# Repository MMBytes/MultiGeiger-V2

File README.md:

# MultiGeiger V2 (ESP-IDF native)

A ground-up C rewrite of the [MultiGeiger](https://github.com/ecocurious2/MultiGeiger) radiation sensor firmware, ported from Arduino / PlatformIO to **native ESP-IDF 6.0**. Runs on **twelve** ESP32 / ESP32-S3 / ESP32-C5 board variants with a wide selection of optional environmental, particulate, noise, and ambient-light sensors. Uploads to **nine** public back-ends and publishes to MQTT (with Home Assistant Discovery) and remote syslog.

See the [releases page](https://github.com/MMBytes/MultiGeiger-V2/releases) for the latest build and per-release notes.

## What it does

- Counts Geiger pulses and computes CPM and µSv/h with a **runtime-selectable tube type** (Si22G / SBM-20 / SBM-19 / Unknown) configured on `/config` — no rebuild required.
- Drives the HV flyback boost converter from on-chip GPIO timing (no Arduino dependency).
- Optional **environmental sensing**: temperature, humidity, pressure, sea-level-adjusted pressure.
- Optional **PM (particulate matter)**: PM1 / PM2.5 / PM4 / PM10 plus number concentrations and typical particle size.
- Optional **noise**: LAeq / LAmin / LAmax dB(A).
- Optional **ambient light**: lux (two sensor families supported).
- Optional **air-quality index**: NOx index from a Sensirion SGP41 (log, `/status` and MQTT/Home Assistant only — no upload target carries it).
- Optional **standalone CSV logging** to a microSD card: one row of every attached sensor's readings per cycle, timestamped from the GNSS clock, for nodes deployed without a network.
- **Battery telemetry** (voltage, state of charge) on boards with an onboard MAX17048 fuel gauge.
- Optional **GNSS position display** — auto-detected PA1010D or MAX-M10S receiver shows fix, satellites, HDOP, lat/lon (OpenStreetMap link), and altitude on `/status`; display-only (NTP is the sole time source).
- Per-cycle upload (default 150 s, configurable 10 s – 1 h) to any subset of **nine** public back-ends.
- **MQTT publish** with 24 Home Assistant Discovery entities, three TLS modes including custom CA.
- **Remote syslog** (UDP 514, RFC 5424) for centralised log aggregation.
- **Hourly FTP/FTPS** upload of the on-device log ring buffer.
- **CPM history graph** on `/status` — 60-minute and 24-hour inline SVG with gridlines and a `HH:MM` time axis; rolling **cpm5 / cpm15** 5- and 15-minute averages fed to GMCMap and ThingSpeak.
- **Web UI** at `http://<device>/` — `/config` (settings), `/status` (live metrics + per-target TX stats + per-sensor presence + CPM graph), `/update` (OTA), `/log` (in-memory log ring). On PSRAM boards, ticking **Serve the web UI over HTTPS** on `/config` (off by default; applies after "Save and restart") moves the UI to `https://<device>/` with a per-device self-signed certificate (`/cert.pem` to import, SHA-256 fingerprint on `/`); port 80 then keeps `/log`, `/api/env` and `/cert.pem` plain and redirects everything else.
- **Crash recovery**: ESP-IDF panic handler writes a coredump to a dedicated flash partition; downloadable post-reboot via `GET /coredump.elf` (no USB required).
- **OLED status display** (SSD1306 128×64, also supports SparkFun SerLCD I²C and NeoPixel tick on supported boards).
- **NTP** with up to three configurable servers and POSIX TZ string.

## Supported hardware

### Boards (twelve build targets)

| Build target | MCU / module | Flash | Notes |
|---|---|---|---|
| `heltec_v2` | Heltec WiFi Kit 32 V2 (ESP32-D0WDQ6) | 8 MB | Onboard SSD1306 OLED. The original target — most production deployments. |
| `heltec_v2_4mb` | Heltec WiFi Kit 32 V2 clone | 4 MB | Same module silicon, smaller flash. Tight on heap during OTA — see V2.4.13 teardown logic in `main.c`. |
| `feathers3_d` | Unexpected Maker FeatherS3 with display (ESP32-S3) | 8 MB | Two STEMMA QT connectors (STEMMA1 on IO8/IO9, STEMMA2 LDO-gated on IO15/IO16). External I²C OLED via STEMMA. PSRAM — WiFi/lwIP/mbedTLS offloaded to PSRAM for sustained heap headroom. |
| `adafruit_qtpy_esp32_pico` | Adafruit QT Py ESP32-PICO | 8 MB | Compact form factor. Optional NeoPixel tick on pulse. PSRAM. |
| `seeed_xiao_esp32s3` | Seeed Studio XIAO ESP32-S3 | 8 MB | Tiny 21×17.5 mm — shares QT Py form factor + Geiger pin map (A0 / A1 / SCK), so one PCB design works for both. Onboard user LED blinks per pulse. PSRAM. |
| `seeed_xiao_esp32s3_wio` | Seeed Studio XIAO ESP32-S3 + Wio-SX1262 kit | 8 MB | The XIAO on Seeed's Wio-SX1262 LoRa board. **Rev C V3 carrier only** (Geiger pulse on the RX pad, since the LoRa SPI bus uses the SCK pad). **LoRaWAN uplink** (V2.8.11+), see below. The XIAO's user LED is not used (its pin is the Wio's button). PSRAM. |
| `heltec_wifi_lora32_v4_r2` | Heltec WiFi LoRa 32 V4 — base/R2 variant (ESP32-S3R2) | 16 MB | Third-party PCB: the standard Multigeiger V2 mainboard populated with this module instead of the Heltec V2. Onboard SSD1315 OLED on a dedicated, always-on I²C bus separate from the env-sensor bus. 2 MB in-package PSRAM. **LoRaWAN uplink** (V2.6.23+) via an onboard SX1262 (RadioLib 8.0, OTAA/Class A) — see the LoRaWAN section below. |
| `sparkfun_thing_plus_esp32s3` | SparkFun Thing Plus ESP32-S3, WRL-24408 (ESP32-S3-MINI-1) | 4 MB | Second-source MCU for the FeatherS3-D-format carrier PCB — same Feather footprint, drop-in alternative to `feathers3_d` on the same board. External I²C OLED via Qwiic, onboard MAX17048 fuel gauge, onboard WS2812 NeoPixel (always-on rail, no power-gate GPIO). 2 MB in-package PSRAM. |
| `sparkfun_thing_plus_esp32c5` | SparkFun Thing Plus ESP32-C5, WRL-30678 (ESP32-C5-WROOM-1) | 8 MB | First single-core/RISC-V target. Its own Thing Plus carrier (not a drop-in for the FeatherS3-D board). External I2C OLED via Qwiic, onboard MAX17048 fuel gauge, onboard WS2812 NeoPixel (always-on rail via pull-up, no power-gate GPIO). 8 MB in-package PSRAM. |
| `adafruit_esp32s3_tft_feather` | Adafruit ESP32-S3 TFT Feather, #5483 (ESP32-S3) | 4 MB | Shares the FeatherS3-D-format carrier PCB. Onboard 240×135 ST7789 color SPI TFT (esp_lcd, 5-page rotation only — no radiation single-page layout) instead of an external I²C OLED; shared TFT/STEMMA-QT power gate on GPIO21. Onboard WS2812 NeoPixel. 2 MB external QSPI PSRAM (feathers3_d-class, not in-package). |
| `adafruit_esp32_feather_v2` | Adafruit ESP32 Feather V2, #5400/#5900 (ESP32-PICO-MINI-02) | 8 MB | Second-source MCU (original ESP32 LX6, not S3) for the Feathers3d_new_pcb shared carrier. External I²C OLED wired to the header SDA/SCL pins, NOT the board's onboard STEMMA QT connector — NEOPIXEL_I2C_POWER only gates that connector's own regulator, and it isn't driven until neopixel_init() runs after sensor/display probing, so a display wired to the connector would never be found. Onboard WS2812 NeoPixel. No fuel gauge, so no battery telemetry (the board's GPIO35 battery divider is not read). 2 MB in-package PSRAM. |
| `adafruit_esp32s3_feather_4mb_2mbpsram` | Adafruit ESP32-S3 Feather, 4MB/2MB PSRAM, STEMMA QT, #5477 (ESP32-S3) | 4 MB | Shares the Feathers3d_new_pcb carrier PCB. No onboard display — external I²C OLED via STEMMA QT, probe-detected. Onboard MAX17048 fuel gauge, onboard WS2812 NeoPixel. Single STEMMA QT I²C bus power-gated on GPIO7 (no always-on bus) — same pattern as `adafruit_esp32s3_tft_feather`'s gate, different GPIO. Onboard red "#13" LED (not the NeoPixel) flashes on each Geiger pulse. 2 MB external QSPI PSRAM (feathers3_d-class, not in-package). |

Every build takes a `-DBOARD=<target>` argument — see [Build from source](#build-from-source). All boards share the same `main/` source tree; differences are isolated in per-board `sdkconfig.defaults.<board>` and HAL pin map. PSRAM boards additionally include `sdkconfig.defaults.psram` (WiFi roaming app + PSRAM offload knobs).

### LoRaWAN uplink (heltec_wifi_lora32_v4_r2 and seeed_xiao_esp32s3_wio)

OTAA/Class A uplink over an SX1262 (RadioLib 8.0; onboard on the Heltec V4, the Wio-SX1262 board on the XIAO ESP32-S3 kit), configured in a dedicated **`/config` LoRaWAN section** (all-region frequency-plan dropdown, DevEUI/JoinEUI/AppKey entry, join status; session keys persist in NVS across reboots). Ports 1 and 2 are byte-identical to the Multigeiger V1.9 Arduino firmware's TTN uplinks — paste `docs/ttn_payload_formatter.js` into TTN Console as a Custom Javascript payload formatter to decode them. While LoRaWAN runs, the upload interval follows the data rate instead of the configured interval (SF7 4 min, SF8 7, SF9 12, SF10 22, SF11 and SF12 30 min), which keeps the radiation frame at SF7–SF10 within TTN's Fair Use Policy of 30 s air time per day (the hourly environment frame and network-ordered repeats add to that); RadioLib's duty-cycle limiter is on as a backstop (EU868: the band's 1 %). The region defaults to AU915 — pick yours (e.g. EU868 in Europe) before enabling.

### Geiger tube

The tube type is a runtime **`/config` dropdown** — no rebuild required to switch tubes:

| Option | cps → µSv/h | Notes |
|---|---|---|
| **Unknown** | — (dose suppressed) | CPM reported; µSv/h field omitted from all uploads |
| **SBM-20** | 1 / 2.47 | Energy-compensated cylindrical tube |
| **SBM-19** | 1 / 9.81888 | Large pancake, lower background |
| **Si22G** | 1 / 12.2792 | **Default** — empirical vs. odlinfo.bfs.de reference |

Calibration factors from the upstream MultiGeiger (`ecocurious2 / t-pi tube.cpp`). The selected tube is shown on the `/status` Radiation card and in the boot config dump. Changing it in `/config` applies live (no reboot). CPM counting, HV timing, and dead-time gating are all tube-agnostic.

### Environmental sensors (auto-detected on I²C)

| Sensor | Address | Provides | Notes |
|---|---|---|---|
| **SHT45** | 0x44 | Temperature, humidity | Sensirion successor to SHT3x. PTFE filter variant supported. |
| **BME280** | 0x76 / 0x77 | Temperature, humidity, pressure | Bosch — original upstream sensor. |
| **BME688** | 0x76 / 0x77 | Temperature, humidity, pressure | Bosch — gas channel currently unused. |
| **BMP390** | 0x76 / 0x77 | Temperature, pressure | Bosch — high-accuracy barometric. |
| **BMP581** | 0x46 / 0x47 | Temperature, pressure | Bosch latest-gen — sub-Pa noise floor. |

The driver mix lets a node combine, e.g., SHT45 (best RH) + BMP581 (best pressure) on the same bus. The firmware picks the right reading per measurand from whichever sensors responded at boot.

### Specialty sensors (auto-detected on I²C)

| Sensor | Address | Provides | Notes |
|---|---|---|---|
| **Sensirion SPS30** | 0x69 | PM1 / PM2.5 / PM4 / PM10 mass, N05–N10 number concentrations, typical particle size | Adds the SPS30_* field group to all upload targets. |
| **hbitter DNMS** | 0x55 | LAeq / LAmin / LAmax dB(A) | Nettigo NAM-style Teensy-based noise module. Adds DNMS_noise_* fields. |
| **ALS-PT19** | (analog) | Ambient light (lux) | Onboard FeatherS3-D photodiode on ADC1_CH3. |
| **VEML7700** | 0x10 | Ambient light (lux) | Vishay I²C, alternative to ALS-PT19. |
| **PA1010D** | 0x10 | GNSS position + time (display-only) | Adafruit 4415 (MediaTek MT3333). Detected by live NMEA sniff — disambiguates from a VEML7700 at the same address. |
| **MAX-M10S** | 0x42 | GNSS position + time (display-only) | SparkFun Qwiic (u-blox DDC). Factory chip serial queried via UBX-SEC-UNIQID and shown on `/status`. |
| **Sensirion SGP41** | 0x59 | NOx index | VOC + NOx gas sensor; only the NOx index is surfaced (log / `/status` / MQTT). Runs its own sampling task — it needs a 1 Hz conditioning cadence. |
| **MAX17048** | 0x36 | Battery voltage, state of charge | Onboard fuel gauge on the FeatherS3-D, SparkFun Thing Plus and Adafruit Feather boards that carry one. |

A microSD socket (SDMMC 4-bit on ESP32-S3 boards, SPI where the chip has no SDMMC host) enables the standalone CSV logger when present; see `main/sd_logger.h` for the file layout.

### Displays

- **SSD1306 OLED** 128×64, I²C 0x3C or 0x3D — auto-probe both addresses (V2.4.19).
- **SparkFun SerLCD** (I²C variant) — alternative line-based display.
- **NeoPixel** tick-per-pulse on supported boards (configurable colour / brightness via `display_mode`).
- Built-in **speaker** click on pulse (configurable, off by default for sealed-tube installs).

## Upload targets

All **nine** targets are fully optional and independently configurable. Each has per-target circuit-breaker logic (V2.3.x) — 3 consecutive all-retry failures suspend that target for 20 cycles to prevent failed TLS handshakes from fragmenting heap.

| Target | Endpoint | Auth | Fields posted |
|---|---|---|---|
| **Madavi** | `api-rrd.madavi.de/data.php` (HTTP / HTTPS) | none | T/H/P; PM and noise are POSTed but the legacy server only graphs T/H/P |
| **sensor.community** | `api.sensor.community/v1/push-sensor-data/` (HTTP / HTTPS) | X-Sensor = chip ID | Radiation (X-PIN 19), T/H/P (11), PM (1), noise (15) — split bodies per pin |
| **Radmon** | `radmon.org/radmon.php?function=submit` (HTTP / HTTPS) | basic auth user/pw | Radiation CPM only |
| **openSenseMap** | `ingress.opensensemap.org/boxes/<BOX_ID>/data?luftdaten=1` (HTTPS) | Box ID in URL + optional raw access token (no `Bearer ` prefix) | Combined Luftdaten body |
| **aqi.eco** | `api.aqi.eco/update/<TOKEN>` (HTTPS) | token in URL | Combined Luftdaten body with `esp8266id` field |
| **GMCMap** | `gmcmap.com/log2.asp` (HTTP only) | Account ID + Geiger counter ID in URL | Radiation CPM + ACPM (5-min rolling average). Skipped when tube disabled. |
| **ThingSpeak** | `api.thingspeak.com/update` (HTTP / HTTPS) | Write API key | field1=CPM, field2=µSv/h, field3=cpm5, field4=cpm15, field5–7=T/H/P. Skipped when tube disabled. |
| **ThingSpeak PM** | `api.thingspeak.com/update` (HTTP / HTTPS) | Separate write API key | field1–4=PM1/PM2.5/PM4/PM10, field5–7=T/H/P, field8=typical particle size. Skipped when no PM sensor. |
| **openSenseMap STAGING** | `upload.staging.opensensemap.org/boxes/<BOX_ID>/data?luftdaten=1` (HTTPS only) | Independent Box ID + access token | Same Luftdaten body as production OSM — lets a node mirror to prod + staging simultaneously. |

Each target shows live per-target stats on `/status` — attempted / succeeded counters, last HTTP status, last attempt time, current breaker state.

Cert verification uses the Mozilla CA bundle baked into flash. Per-target "insecure mode" available for self-hosted instances. TLS 1.2 and TLS 1.3 both supported.

## Observability

### MQTT (V2.4.2–V2.4.6)

Publish-only MQTT 3.1.1 client with three TLS modes:

- **Mode 0** — plain TCP (broker on LAN)
- **Mode 1** — TLS via Mozilla CA bundle (public broker)
- **Mode 2** — TLS via user-supplied custom CA PEM (self-signed broker, e.g. a Pi running Mosquitto on the LAN)

When `mqtt_ha_discovery` is enabled (default), the firmware publishes 24 Home Assistant Discovery entities at boot — radiation, all detected sensors, WiFi RSSI, per-target TX stats, etc. — auto-gated on driver presence. HA picks them up without manual configuration.

Topic layout: `<prefix>/<chip-id>/state` (full state JSON every cycle) plus `<prefix>/<chip-id>/availability` for the LWT.

### Syslog (V2.4.15)

UDP syslog client (port 514, configurable). **RFC 5424** framing with `local0` facility. Every applog line mirrors to syslog when enabled. Before the wall clock is valid (pre-NTP sync), the timestamp is the NILVALUE `-` — a stock rsyslog collector falls back to its own receive time, correctly dating boot-banner and config-dump lines. Once NTP has synced, the timestamp is local RFC 3339 with a numeric UTC offset (e.g. `2026-06-13T20:45:50+10:00`), matching the in-message device time shown on `/status`. The per-cycle log line reports `syslog udp: tx=N drops=M` so device-side UDP packet loss is visible (V2.5.29).

### FTP / FTPS log upload (V2.0.x +)

Configurable interval (1 min – 10 090 min, ~7 days; default hourly) upload of the on-device log ring buffer to an FTP server. TLS supported (FTPS explicit-mode, AUTH TLS, TLS 1.2 and 1.3 both work). Cleared after successful upload; carried over across reboot via NVS.

### CPM history graph (V2.5.6)

Two-tier in-RAM ring: 60 one-minute samples + 24 one-hour samples (~250 bytes, all boards). Sampled from a monotonic pulse counter independent of the destructive per-cycle `tube_read()`, so the TX interval has no effect on graph resolution. Displayed as an **inline SVG** on `/status` with horizontal CPM gridlines and a `HH:MM` time axis. Also drives the **cpm5 / cpm15** rolling averages (means of the last 5 / 15 minute samples), fed to GMCMap as ACPM and to ThingSpeak as field3 / field4.

### Coredump on panic (V2.4.18)

64 KB dedicated coredump partition. The ESP-IDF panic handler writes the panicking task's register state + stack snapshot before reset. Recoverable post-reboot via `GET /coredump.elf` (basic auth gated) — no USB needed once flashed. Decode with `espcoredump.py`.

## Security

V2.3.33 web security audit + V2.4.x follow-ups (see CHANGELOG):

- **Basic auth** on `/config`, `/update`, `/reboot`, `/coredump.elf` (user `admin`, password = configured AP password).
- **Constant-time password comparison** to defeat timing oracles.
- **CSRF protection**: POSTs to `/config` / `/update` / `/reboot` require an `Origin` header matching the device's URL — protects against drive-by browser POSTs. **Note for curl users**: add `-H "Origin: http://device:port"` or you'll get a 403.
- **OTA size clamp**: rejects an image larger than the target OTA slot before writing (2 MB on 8 MB-flash boards, 1.875 MB on 4 MB-flash boards).
- **X-Frame-Options: DENY** on all responses.
- **TX is paused during OTA** (V2.4.24): scheduled cycles skip while an OTA upload is in progress, giving the OTA the full WiFi airtime.

- **HTTPS for the device UI** (V2.8.0, PSRAM boards): optional, per-device self-signed certificate, see "What it does" above.

Deferred for future work: signed OTA images, NVS encryption, rate limiting. The device is designed for a trusted LAN; do not expose it to the internet.

## Installation

### Flashing a prebuilt release (no build environment needed)

Every [release](https://github.com/MMBytes/MultiGeiger-V2/releases) attaches per-board artefacts. Pick the bundle that matches your board — see the release notes for the file naming.

**Browser-based first flash (no tools needed):** The [MultiGeiger-V2 web flasher](https://mmbytes.github.io/MultiGeiger-V2/) supports Chrome / Edge via the WebSerial API — connect the board over USB, select your board, and flash the latest release directly from the browser.

**`esptool` first flash:** Install [`esptool`](https://github.com/espressif/esptool) (`pip install esptool`); replace `COM3` with your actual serial port.

**First flash of a blank / fresh / bricked device — use `geiger_v2_merged_<board>.bin`:**

```
esptool --chip esp32 --port COM3 write-flash 0x0 geiger_v2_merged_heltec_v2.bin
```

Use `--chip esp32s3` for the ESP32-S3 boards and `--chip esp32c5` for the SparkFun Thing Plus ESP32-C5. FeatherS3-D additionally needs `--before no-reset --after no-reset` and the BOOT+RST button dance.

The merged image bundles the bootloader, partition table, OTA slot pointer, and the app at their correct flash offsets — a single-file factory flash. Each release also attaches the separate parts (`bootloader_<board>.bin`, `partition-table_<board>.bin`, `ota_data_initial_<board>.bin`), the matching debug symbols (`elf_<board>.zip`, for decoding a coredump) and a `SHA256SUMS` file.

**Upgrading a device already running this firmware:**

- **OTA (recommended)** — browse to `http://<device-ip>/update`, log in (`admin` / your configured AP password), pick the `geiger_v2_<board>.bin` artefact for your board. No cable, keeps your NVS (WiFi credentials, MQTT broker, etc.) intact.
- **Board revision matters**: the firmware has no runtime board-revision detection. Before flashing an older carrier or mainboard, read the compatibility table in [`Hardware/README.md`](Hardware/README.md).

### First boot

The device comes up as a WPA2-protected WiFi access point named after its chip ID (`esp32-<number>`, e.g. `esp32-1234567`). The AP password is the configured AP password — `ESP32Geiger` on a fresh device. Join it, browse to `http://192.168.4.1/config`, and set WiFi credentials, the AP/admin password and your back-end choices. The AP stays up for about two minutes after boot; after that window, or a manual reboot, the device joins your network in STA mode.

Default credentials (change these on first login — the same password protects the web UI and the setup AP):

| Field | Default |
|---|---|
| Username | `admin` |
| Password | `ESP32Geiger` |

**Locked out of the web page?** After 5 wrong passwords in a row the node refuses every login for a while, the correct password too (1 minute at first, doubling with each further lock up to 8 h 32 min). Wait until the time shown has passed, or press the reset button or unplug the node for about 10 seconds; that clears the lock.

**Stored passwords on `/config`:** the page never shows them. A field shows `******** SECRET SET ********` when a value is stored; leave it empty to keep it, enter `-` to clear it, or type a new value.

## Build from source

Needed only if you want to modify the firmware.

### Requirements

- [ESP-IDF v6.0.3](https://docs.espressif.com/projects/esp-idf/en/stable/esp32/get-started/index.html) — pure IDF, not arduino-esp32, not PlatformIO. Releases are built with exactly v6.0.3; CMake warns if a different IDF is in use.
- A Windows / Linux / macOS host with the IDF tools installed
- USB cable with data lines

### Commands

With the IDF environment sourced (`export.ps1` on Windows, `export.sh` on Linux/macOS):

```
idf.py -B build_heltec_v2 -DBOARD=heltec_v2 build
idf.py -B build_heltec_v2 -DBOARD=heltec_v2 -p <PORT> flash monitor
idf.py -B build_heltec_v2 -DBOARD=heltec_v2 merge-bin -o geiger_v2_merged_heltec_v2.bin   # single-file factory image
```

`-DBOARD=` selects the chip target, the board macros and the per-board `sdkconfig.defaults.<board>` overlay in one go — do not pass `SDKCONFIG_DEFAULTS` yourself. Substitute `heltec_v2_4mb`, `feathers3_d`, `adafruit_qtpy_esp32_pico`, `seeed_xiao_esp32s3`, `seeed_xiao_esp32s3_wio`, `heltec_wifi_lora32_v4_r2`, `sparkfun_thing_plus_esp32s3`, `sparkfun_thing_plus_esp32c5`, `adafruit_esp32s3_tft_feather`, `adafruit_esp32_feather_v2`, or `adafruit_esp32s3_feather_4mb_2mbpsram` for other boards, and use a matching `-B build_<board>` directory: the generated `sdkconfig.<board>` cache is per board, so boards never pollute each other.

Host-side unit tests for the pure helpers need only a C compiler:

```
gcc -I main -Wall -Wextra -Werror -std=c11 -o test/run test/test_main.c && ./test/run
```

(`_test.cmd` wraps the same on Windows.) Static analysis runs in CI with cppcheck 2.22.0, one leg per board.

Optional: `git config core.hooksPath .githooks` enables a pre-commit scan that refuses to commit private-network data (LAN/MAC/hostname shapes) — the same check CI runs on every push.

### Release workflow

`git tag -a V2.X.Y && git push --tags` is the release ceremony. GitHub Actions `release.yml` first runs the cheap gates (host tests, cppcheck on every board, a `## V2.X.Y` section present in `CHANGELOG.md`), then builds all twelve boards (each build also verifies that `VERSION_STR` equals the tag and that the image fits its OTA slot), creates the GitHub Release with the artefacts, `SHA256SUMS` and the CHANGELOG section as body, and finally publishes the web flasher — only if the tag is the newest release, so re-running an old tag never rolls the flasher back.

## Repository layout

```
main/                       firmware C sources
  main.c                    entry point, WiFi state machine, cycle loop
  tube.c                    pulse ISR + HV driver timing
  tube_types.c / .h         tube characteristics table (cps→µSv/h factors per tube type)
  tube_pcnt.c / .h          optional PCNT width-filter for narrow-pulse characterisation
  tube_logic.h              pure inline helpers: clamp_u32, gmc_classify, guard policy
  config.c / config_fields.def
                            NVS-backed config, X-macro schema
  http_server.c             web UI (/, /config, /status, /update, /log, /coredump.elf)
  transmission.c            upload pipeline: Madavi / SC / Radmon / OSM / aqi / GMC / ThingSpeak
  mqtt.c / mqtt_discovery.c MQTT 3.1.1 publish + HA Discovery
  syslog.c                  RFC 5424 UDP syslog client
  log_ftp.c                 FTP/FTPS log upload
  net_arp.c                 gratuitous ARP (mesh-AP blackhole prevention)
  periodic.c                housekeeping (PSA refresh + ARP safety-net)
  coredump.c                /coredump.elf streaming from partition
  ntp.c                     SNTP with configurable POSIX TZ string
  history.c / .h            in-RAM CPM history ring + cpm5/cpm15 rolling averages
  gnss.c / .h               GNSS driver: PA1010D + MAX-M10S auto-detected, display-only
  env_sensor.c              umbrella for T/H/P drivers
  sht45.c bmp581.c bmp390.c bme688.c bme280.c
                            individual T/H/P drivers
  pm_sensor.c sps30.c       particulate matter
  noise_sensor.c dnms.c     noise (DNMS / NAM)
  als.c veml7700.c          ambient light
  sgp41.c                   SGP41 NOx index (+ sensirion_crc.h, sensirion_gas_index_algorithm.c)
  fuel_gauge.c              MAX17048 battery fuel gauge
  sd_card.c sd_logger.c     microSD mount + standalone CSV logger
  lorawan.cpp lorawan_codec.h
                            LoRaWAN uplink (heltec_wifi_lora32_v4_r2, seeed_xiao_esp32s3_wio)
  telemetry.c / .h          sensor-reading registry shared by SD logger and status
  env_api.h                 /api/env JSON contract (served by http_server.c)
  tls_cert.c / tls_logic.h  per-device HTTPS certificate (generation, NVS storage)
  display.c display_tft.c display_serlcd.c neopixel.c led.c
                            display drivers (OLED / ST7789 TFT / SerLCD) + LED pulse-tick
  speaker.c / speaker_logic.h
                            pulse tick (boards with speaker)
  i2c_bus.c                 shared I²C bus handle + mutex
  applog.c                  in-memory log ring buffer
  diag.c / .h               I²C error counter + per-cycle heap split logging
  util.h                    clamped string helpers, URL encoding
  hal.h                     per-board pin map + capability flags
  sysinfo.h                 chip model string, reset-reason string
  main_status.h             request-restart IPC (main loop ← HTTP/TX workers)
partitions.csv              factory + dual-OTA (2 MB each) + coredump (64 KB) on 8 MB flash
partitions_4mb.csv          dual-OTA (1.875 MB each) + coredump for the four 4 MB-flash boards
                            (heltec_v2_4mb, sparkfun_thing_plus_esp32s3,
                            adafruit_esp32s3_tft_feather, adafruit_esp32s3_feather_4mb_2mbpsram)
sdkconfig.defaults.<board>  per-board IDF configuration
sdkconfig.defaults.psram    shared WiFi-roaming app + PSRAM-offload knobs (PSRAM boards)
CHANGELOG.md                per-release WHAT/WHY notes
docs/                       web flasher (index.html + manifests/ + vendored esp-web-tools),
                            TTN payload formatter
.github/workflows/          build.yml, release.yml, repo-checks.yml + the reusable
                            _host-test / _cppcheck / _build-boards gates
.github/scripts/            board-list consistency check, private-data scan,
                            CHANGELOG section extractor

Hardware/                   PCB design files — see Hardware/README.md for the
                            revision → board → minimum-firmware map
  Revision_A/               MultiGeiger V1.10 mainboard for the Heltec WiFi LoRa 32 V4 (Eagle)
  Revision_B/               FeatherS3-D-format carrier PCB (KiCad 8)
    geiger.kicad_pro / .kicad_pcb / .kicad_sch
                            KiCad 8 project sources
    0_Custom_Library.pretty / geiger.pretty
                            custom symbol + footprint libraries
    3d-Files/               3D STEP models for non-trivial parts
    Deliverables/
      Gerber Files/         fab-ready Gerbers
      Pick And Place Files/ assembly CSVs
      BOM/                  bill of materials
      Schematic/            schematic PDF
      Renderings/           3D rendered previews
      Supporting Files/     STEP export
  Revision_C/               shared-footprint PCB: QT Py ESP32-PICO or XIAO ESP32-S3
    (same sub-structure as Revision_B)
```

## PCB design files

Three PCB revisions are included in the `Hardware/` directory. [`Hardware/README.md`](Hardware/README.md) maps each revision to the modules it carries and the **minimum firmware** it needs — read it before flashing an older board.

### Revision A — MultiGeiger V1.10 mainboard

[`Hardware/Revision_A/`](Hardware/Revision_A/) is the Eagle project for the V1.10 iteration of the upstream MultiGeiger mainboard, re-laid for the Heltec WiFi LoRa 32 V4 (R2) module (`heltec_wifi_lora32_v4_r2` firmware, V2.7.1 or later), with Gerbers, pick-and-place CSV, BOM, schematic PDF and renderings.

- **Browse the schematic**: [`Hardware/Revision_A/Deliverables/Schematic/geiger-v2.pdf`](Hardware/Revision_A/Deliverables/Schematic/geiger-v2.pdf)

### Revision B — FeatherS3-D-format carrier

[`Hardware/Revision_B/`](Hardware/Revision_B/) is the full KiCad 8 project for the Feather-format carrier PCB (FeatherS3-D, SparkFun Thing Plus ESP32-S3 and the three Adafruit Feather targets share it), plus fabrication-ready Gerbers, pick-and-place CSVs, schematic PDF, BOM, and 3D STEP exports. Si22G tube; full BOM uses metal-film resistors and polypropylene HV capacitors throughout.

- **Browse the schematic**: [`Hardware/Revision_B/Deliverables/Schematic/geiger.pdf`](Hardware/Revision_B/Deliverables/Schematic/geiger.pdf)
- **3D renderings**: [`Hardware/Revision_B/Deliverables/Renderings/`](Hardware/Revision_B/Deliverables/Renderings/)
- **Re-fabricate at JLCPCB or similar**: upload the Gerbers + PnP CSV from `Deliverables/` directly, or open the `.kicad_pro` to regenerate

### Revision C — shared QT Py / XIAO footprint

[`Hardware/Revision_C/`](Hardware/Revision_C/) is a shared-footprint PCB that accepts either the Adafruit QT Py ESP32-PICO or the Seeed XIAO ESP32-S3 in the same U1 socket — both use the same Geiger pin map (HV_FET / GMC / interrupt on A0 / A1 / SCK), so one board runs both `adafruit_qtpy_esp32_pico` and `seeed_xiao_esp32s3` firmware builds. Same HV circuit as Revision B; no piezo (sealed-tube form factor). On-board Qwiic / STEMMA QT connector with on-board pull-ups.

- **Browse the schematic**: [`Hardware/Revision_C/Deliverables/Schematic/geiger.pdf`](Hardware/Revision_C/Deliverables/Schematic/geiger.pdf)
- **3D renderings**: [`Hardware/Revision_C/Deliverables/Renderings/`](Hardware/Revision_C/Deliverables/Renderings/)
- **Re-fabricate**: upload Gerbers + PnP CSV from `Revision_C/Deliverables/`

**License** for all three revisions: same GPL-3.0-or-later as the firmware.

## Documentation

- **Per-release notes**: [`CHANGELOG.md`](CHANGELOG.md) — full WHAT/WHY for every release since V2.3.23, headlines for older. GitHub release pages have the rest.
- **In-firmware**: `/status` shows live state including which drivers responded at boot, per-target TX stats, FTP / MQTT / syslog status, CPM history graph, and GNSS position if a receiver is detected.

## Attribution

This firmware is an **independent rewrite** of [MultiGeiger](https://github.com/ecocurious2/MultiGeiger) by the ecocurious2 project. Hardware design, sensor-community protocol compatibility, the Si22G calibration constant, and the upload-target conventions come from upstream; the C source in this repository shares no commits with it.

The MQTT / HA Discovery, MQTT TLS modes, openSenseMap support, aqi.eco support, GMCMap support, ThingSpeak support, syslog (RFC 5424), coredump-to-flash, multi-board build (FeatherS3 / QT Py / XIAO), runtime-selectable tube type, PCNT width filter, dead-time guard, CPM history graph and rolling averages, GNSS display, and most of the additional sensor drivers (SHT45, BMP581, BMP390, BME688, SPS30, DNMS, ALS-PT19, VEML7700, PA1010D, MAX-M10S) are net-new in V2.

## License

**GPL-3.0-or-later** — same as upstream MultiGeiger. See [LICENSE](LICENSE).

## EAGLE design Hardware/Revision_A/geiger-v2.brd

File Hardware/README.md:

# Hardware

PCB designs that the MultiGeiger V2 firmware runs on. Three revisions are
tracked. Each is a complete design with fabrication outputs under its
`Deliverables/` folder: Gerbers (plus an order-ready zip), pick-and-place
CSV, BOM, schematic PDF and 3D renderings.

## Revision → board → firmware

| Directory | Board | Module it carries | Firmware target(s) | Minimum firmware | Tool |
|---|---|---|---|---|---|
| `Revision_A/` | MultiGeiger mainboard **V1.10** | Heltec WiFi LoRa 32 V4, base/R2 variant | `heltec_wifi_lora32_v4_r2` | **V2.7.1** | Eagle (`geiger-v2.sch` / `.brd`) |
| `Revision_B/` | FeatherS3-D-format carrier, **V2 layout** | Unexpected Maker FeatherS3-D, SparkFun Thing Plus ESP32-S3, Adafruit ESP32-S3 TFT Feather, Adafruit ESP32 Feather V2, Adafruit ESP32-S3 Feather #5477 | `feathers3_d`, `sparkfun_thing_plus_esp32s3`, `adafruit_esp32s3_tft_feather`, `adafruit_esp32_feather_v2`, `adafruit_esp32s3_feather_4mb_2mbpsram` | **V2.6.34** | KiCad 8 |
| `Revision_C/` | Shared-footprint carrier, **V2 layout** | Adafruit QT Py ESP32-PICO **or** Seeed XIAO ESP32-S3 in the same U1 socket (the XIAO ESP32-S3 + Wio-SX1262 kit needs the V3 layout, see below) | `adafruit_qtpy_esp32_pico`, `seeed_xiao_esp32s3` (V3 layout: also `seeed_xiao_esp32s3_wio`) | **V2.6.34** | KiCad 8 |

Not in this directory:

- The Heltec WiFi Kit 32 V2 targets (`heltec_v2`, `heltec_v2_4mb`) run on the
  upstream [ecocurious2 MultiGeiger](https://github.com/ecocurious2/MultiGeiger)
  mainboard (V1.4, Eagle files in that repository's `docs/hardware/`).
- The SparkFun Thing Plus ESP32-C5 target has its own carrier; that design is
  not published here.

## Firmware compatibility — read before flashing

There is no runtime board-revision detection: **the firmware version is the
cutover line.** The pin maps live in `main/hal.h`, whose header comment is
the authoritative statement of this rule.

- **Rev B V2 and Rev C V2 layouts (the files tracked here)** need firmware
  **≥ V2.6.34**. That release moved the Geiger count and HV-FET signals to
  different socket pads to remove HV-to-counter crosstalk.
- **The original (pre-V2) Rev B / Rev C layouts** must stay on firmware
  **≤ V2.6.33**. Flashing a newer build onto an original carrier drives the
  HV FET PWM into the tube pickup and reads "counts" off the FET gate trace.
  Those layouts are superseded and not tracked.
- **Rev C V3 layout** (not yet published here) moves the Geiger count signal
  from socket pad 9 (SCK) to pad 8 (RX), so that pads 9 to 11 are free for an
  SPI add-on such as the Wio-SX1262 LoRa board on the XIAO ESP32-S3. It needs
  firmware **≥ V2.8.10** with `/config` → **Rev C carrier = V3**. The setting
  defaults to V2, so a Rev C V2 carrier needs no change. It must match the
  carrier. The XIAO ESP32-S3 + Wio-SX1262 kit has its own firmware target,
  `seeed_xiao_esp32s3_wio` (≥ **V2.8.11**), which is built for the V3 layout
  only and has no carrier setting.
- **V1.10 mainboard (Revision A)** needs firmware **≥ V2.7.1**. V2.6.34 was
  written against a pre-fabrication pad assignment that was never
  manufactured, so for this target V2.6.34 matches no physical board.
- **V1.9 mainboard** (an earlier third-party respin for the same module, not
  tracked) stays on **≤ V2.6.33**.

The browser flasher always installs the latest release, so it is only
suitable for the Rev B V2 / Rev C V2 layouts, the Rev C V3 layout and the
V1.10 mainboard.

## Provenance

- **Revision A** is the V1.10 iteration of the upstream MultiGeiger mainboard
  lineage (ecocurious2 V1.4 → a third-party V1.9 respin for the Heltec WiFi
  LoRa 32 V4 module → this V1.10 rework: HV_CAP_FULL moved from GPIO2 to
  GPIO3 and GMC_COUNT to GPIO6 — the V2.6.34 design had those two the other
  way round and was never built — piezo on GPIO4/5). Kept in Eagle like its
  ancestors.
- **Revision B** and **Revision C** are this project's own KiCad 8 designs.
  They keep the upstream HV topology (flyback boost, zener-regulated rail,
  Si22G tube) and add module sockets, a Qwiic / STEMMA QT connector and
  (Rev C) a sealed, speaker-less form factor. The "V2 layout" of each is the
  current file; the first layout was replaced after the crosstalk
  investigation described in `main/hal.h`.

BOM part numbers are maintained at the source — the Revision A BOM is
generated, the Revision B / C part numbers live in a schematic field pushed
to the footprints — so edit there, not in the exported CSVs.

## Licence

All three designs: **GPL-3.0-or-later**, the same licence as the firmware
and as the upstream MultiGeiger project they descend from. See the
repository [LICENSE](../LICENSE). Upstream attribution: ecocurious2 /
MultiGeiger.

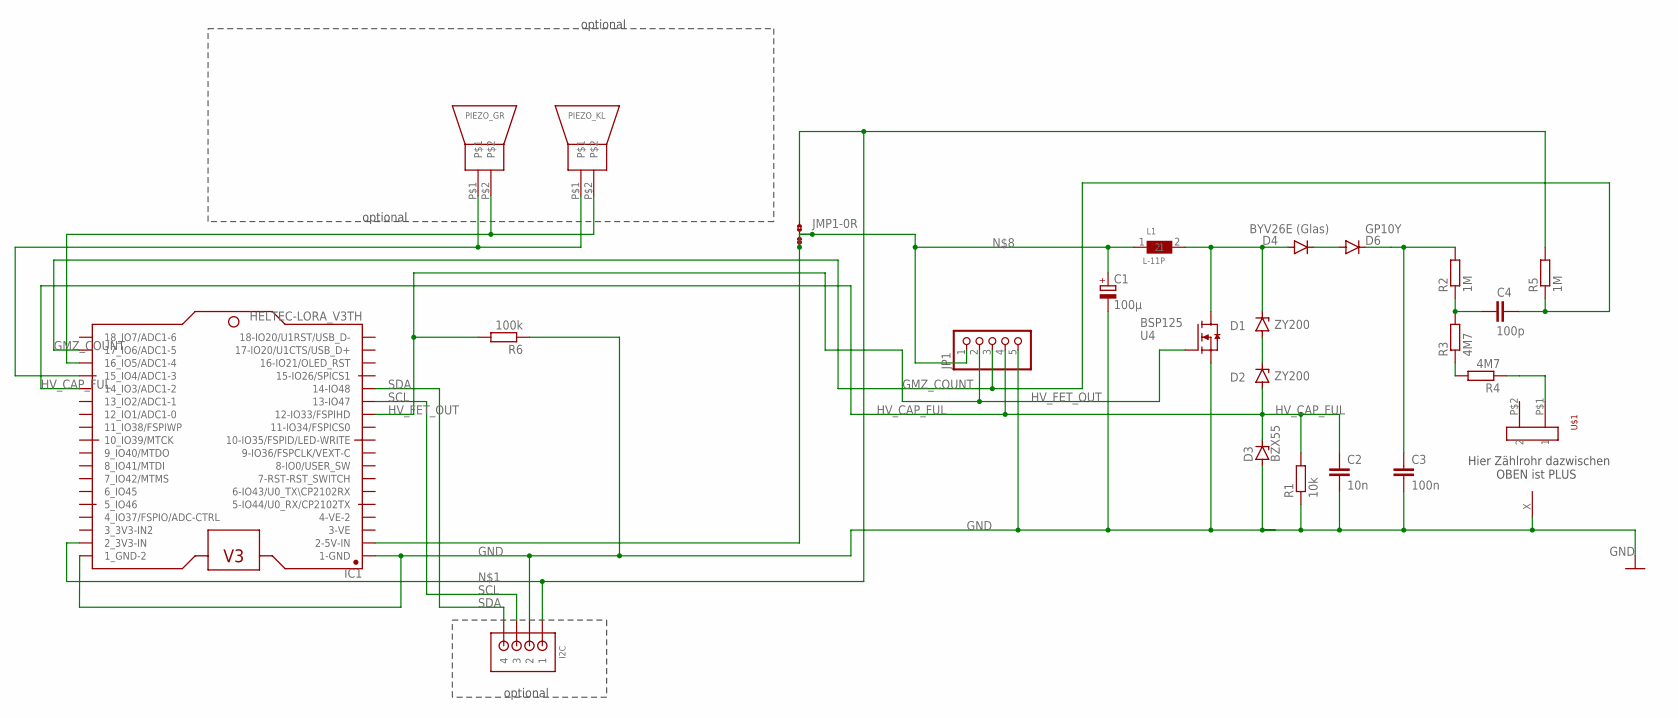
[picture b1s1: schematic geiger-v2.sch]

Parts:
C1: 100µ; E2-5
C2: 10n; C050-035X075
C3: 100n; C150-072X183
C4: 100p; C050-045X075
D1, D2: ZY200; DO41Z10
D3: BZX55; DO35Z10
D4: BYV26E (Glas); DO41-10
D6: GP10Y; DO41-10
I2C: B4B-ZRSIDE_ENTRY; S4B-ZR
IC1: HELTEC-LORA_V3TH; HELTEC_LORA_32
JMP1: 0R-JUMPB; B0R-JMP
JP1: PINHD-1X5; 1X05
L1: L-11P
PIEZO_GR: PIEPSER_BIG
PIEZO_KL: PIEPSER
R1: 10k; 0207/10
R2, R5: 1M; 0207/10
R3, R4: 4M7; 0207/10
R6: 100k; 0207/10
U4: BSP125; SOT223
U$1: FUSE_HOLDER
U$5: ONE_PAD

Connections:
3_3V3-IN2: IC1.3_ (3_3V3-IN2)
GMZ_COUNT: C4.2, IC1.17_ (17_IO6/ADC1-5), JP1.3, R5.1
GND: C1.-, C2.2, C3.2, D3.A, I2C.2, IC1.1- (1-GND), IC1.1_ (1_GND-2), JP1.5, R1.1, R6.1, U4.3 (S), U$5.X
HV_CAP_FUL: C2.1, D2.A, D3.C, IC1.14_ (14_IO3/ADC1-2), JP1.4, R1.2
HV_FET_OUT: IC1.12- (12-IO33/FSPIHD), JP1.2, R6.2, U4.1 (G)
unnamed: I2C.1, IC1.2_ (2_3V3-IN), JMP1.1, R5.2
unnamed: D1.A, D2.C
unnamed: D1.C, D4.A, L1.2, U4.2 (D), U4.4 (D)
unnamed: C3.1, D6.C, R2.2
unnamed: R4.1, U$1.P$1 (1)
unnamed: R3.1, R4.2
unnamed: C4.1, R2.1, R3.2
unnamed: C1.+, IC1.2- (2-5V-IN), JMP1.2, JMP1.3, JP1.1, L1.1
unnamed: D4.C, D6.A
unnamed: IC1.16_ (16_IO5/ADC1-4), PIEZO_GR.P$2, PIEZO_KL.P$2
unnamed: IC1.15_ (15_IO4/ADC1-3), PIEZO_GR.P$1, PIEZO_KL.P$1
SCL: I2C.3, IC1.13- (13-IO47)
SDA: I2C.4, IC1.14- (14-IO48)

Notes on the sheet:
Hier Zählrohr dazwischen OBEN ist PLUS
optional

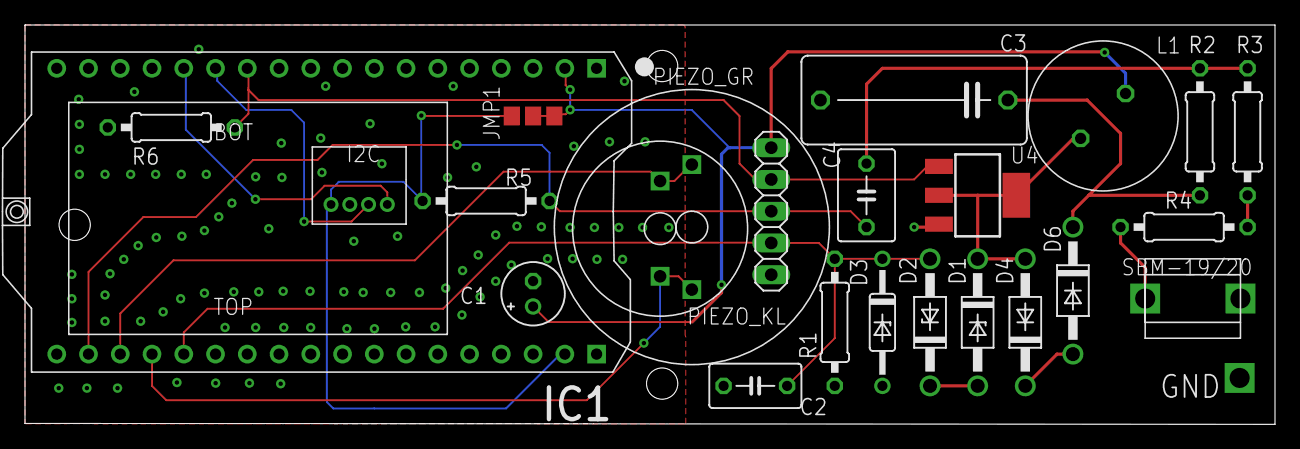
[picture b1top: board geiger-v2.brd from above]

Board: 2 copper layers, 100.0 x 31.9 mm, 25 parts (0 on the bottom side), 17 nets.

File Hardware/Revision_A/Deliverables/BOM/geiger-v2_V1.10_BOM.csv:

Reference,Qty,Value,Package,Part Number
C1,1,100uF/16V,"Through Hole,D5mm,P=2mm",
C2,1,10nF/100V,"Through Hole,P=5mm",MKP2D021001B00KSSD
C3,1,100nF/630V,"Through Hole,P=15mm",R75PI3100AA30J
C4,1,100pF/1000V,"Through Hole,P=5mm",FKP2O101001D00JSSD
"D1,D2",2,ZY200,DO-41,ZY200
D3,1,BZX55C3V3,DO-35,BZX55C3V3-TR
D4,1,BYV26E (Glas),DO-41,BYV26E
D6,1,GP10Y,DO-41,GP10Y
I2C,1,I2C 3V3 - JST ZR or direct wire (optional),"JST ZR,1.5mm,4-pin,side entry,THT",
IC1,1,Heltec WiFi LoRa 32 V4 (R2),"2x18 THT socket strip,P=2.54mm",
JMP1,1,0R,"SMD solder jumper,3-pad",
JP1,1,Header 1x5 - MCU breakout (optional),"Through Hole,P=2.54mm",
L1,1,150mH,"Through Hole,P=5mm",11P-154J-50
PIEZO_GR,1,PIEPSER_BIG (fit ONE piezo only; body covers JP1),"Through Hole,P=10mm",
PIEZO_KL,1,PIEPSER_small (fit ONE piezo only),"Through Hole,P=7.62mm",CPT-1495CI-300
R1,1,10k,"Axial 0207,P=10.16mm",UXB02070F1002AR100
"R2,R5",2,1M,"Axial 0207,P=10.16mm",MFR-25FBF52-1M
"R3,R4",2,4M7,"Axial 0207,P=10.16mm",MFR-25FBF52-4M7
R6,1,100k,"Axial 0207,P=10.16mm",
U$1,1,Tube holder SBM-19/20,"Fuse clip,2x THT,P=7.62mm",
U$5,1,GND wire pad,"Single THT pad,D1.6mm",
U4,1,BSP125,SOT223,BSP125H6327

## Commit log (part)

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2026-04-29 V2.1.20: per-channel oversampling tuned to manufacturer accuracy presets
    Followup to V2.1.19's forced-mode + IIR-off architecture cleanup. Now that
    oversampling does the per-read averaging exclusively (no IIR), tuning the
    per-channel oversampling to Bosch's "Indoor navigation" / "drone" presets
    (and the BME680 application note BST-BME680-AN014) gives measurable noise
    reduction where it actually matters.
    | Sensor | T (was -> now) | P (was -> now) | H (was -> now) |
2026-05-08 V2.3.1: Sensirion SPS30 driver (hand-rolled pure-IDF I2C)
    Adds particulate-matter sensing support — SPS30 only, more PM sensors
    can be slotted into the new pm_sensor facade later. No transmission
    integration yet; SPS30 readings are logged once per cycle. Madavi /
    sensor.community uploads land in V2.3.2.
    - main/sps30.{h,c}: pure-IDF driver, no Sensirion library dependency.
    - I2C address 0x69, 100 kHz bus, shared with env_sensor.
2026-05-09 V2.3.8: Madavi SPS30 visibility hack (SDS_P1 / SDS_P2 alias)
    Madavi's data.php is a 2017-vintage backend that only recognises
    PPD42NS / SDS011 / PMS / HPM / DHT / BMP / BMP280 / BME280 / HTU21D /
    DS18B20 / GPS / signal field-name prefixes. SPS30_*, Si22G_*,
    DNMS_noise_* are silently dropped (no matching $has_* checks -> no
    RRD update -> no Grafana graph). Confirmed by reading data.php
    directly (https://github.com/opendata-stuttgart/madavi-api/blob/master/data.php).
2026-05-09 V2.3.14: OTA upload form shows board-specific prompt with bold-red name
    The /update page's prompt was previously a generic
    "Select a firmware .bin (from firmware_releases/ or build/geiger_v2.bin)."
    which gave the user no clue which board's binary to grab from the
    GitHub release page.
    V2.3.14 makes the prompt board-specific:
    heltec_v2: "Select a firmware .bin for **Heltec WiFi Kit 32**."
2026-05-11 V2.3.21: V1 boot melody + OLED TX-status wiring (V1 parity)
    Two small features bringing V2 in line with what V1 (Git_Repository_Geiger)
    shipped from day one but V2 had quietly dropped during the native-IDF rewrite.
    1. V1 boot melody when play_sound=true (~3.5 s tune):
    D-E-F#-G | D-E-D | B-C-B. Replaces V2's "two quick clicks" boot chirp.
    Replicated note-for-note from V1's speaker.cpp — same frequencies (× 0.75
    scaling baked in to put the notes in the piezo's sweet spot), same
2026-05-13 V2.3.27: FeatherS3-D pin map — HV_FET + speaker moved off A2..A4
    PCB harness rev frees the contiguous A2..A4 trio (only guaranteed ADC-capable
    trio on the Feather form factor) for future analog expansion:
    PIN_HV_FET_OUTPUT : A2 (IO14) -> A5 (IO5)
    PIN_SPEAKER_P : A3 (IO12) -> D10 (IO3) <- ESP32-S3 boot strap
    PIN_SPEAKER_N : A4 (IO6 ) -> D9 (IO1)
    IO3 is the ESP32-S3 JTAG-source strap (HIGH at boot = USB-Serial-JTAG to
2026-05-17 test+ci: T1 host unit tests + T3 cppcheck + T4-lite fuzz + valgrind
    Post-V2.4.1 WIP. Pure CI / testing infrastructure — zero firmware
    binary change (feather still builds at 0x12C8E0 byte-identical to
    V2.4.1). VERSION_STR unchanged.
    (T1) Host-side unit tests.
    - Moved 4 pure helpers (ct_memcmp, hex_nibble, url_decode, html_esc)
    from inline `static` in http_server.c to `static inline` in
2026-05-17 V2.4.3: MQTT Phase 2 (HA Discovery) + 2 latent warnings + PSA kconfig fix
    Adds Home Assistant MQTT Discovery so HA auto-creates one sensor
    entity per present reading on first connect. No manual YAML. Plus
    two pre-existing -Wunused-variable warnings that CI's full build
    log surfaced (V2.4.2 didnt touch those files), and the lost-since-
    v6.0 PSA key-slot count setting.
    HA Discovery (Phase 2 of 3):
2026-05-18 V2.4.7: hotfix — revert MBEDTLS_DYNAMIC_BUFFER on Heltec (FTPS panic)
    V2.4.5 enabled CONFIG_MBEDTLS_DYNAMIC_BUFFER=y on the Heltec overlays
    for ~15-20 KB of transient heap headroom. Bench testing 2026-05-18
    caught a regression: every FTPS upload triggers a TLSF heap-corruption
    panic on Heltec V2.
    Decoded backtrace:
    log_ftp.c:287 io_close()
2026-05-19 V2.4.14: extend OTA teardown pattern to FTPS
    Same fix as V2.4.13's POST /update teardown, gated on FTPS upload start
    instead. Before do_ftp_upload(), call mqtt_stop() to free ~18-25 KB of
    MQTT TLS session state. main.c poll re-inits MQTT within ~1s of FTPS
    completion.
    Observation driving the fix (2026-05-19 production logs):
    esp32-176432 (4MB) cycle #6 - SUCCESSFUL FTPS upload:
2026-05-21 V2.4.19: gratuitous ARP on reconnect + 24h safety-net, SSD1306 0x3D fallback
    Closes the post-roam MQTT-stuck failure mode observed 2026-05-21 on
    esp32-5963724 where mosquitto-to-sensor SYN-ACK was 100% blackholed at
    the mesh-AP bridge after a WiFi reason=34 drop. New net_arp module
    broadcasts a gratuitous ARP on each GOT_IP (deferred to the next
    tx_is_idle tick) and as a 24h safety-net piggy-backed on the existing
    PSA crypto refresh. Also extracts both 24h chores (PSA refresh + ARP)
2026-05-23 README: refresh for current firmware scope
    The previous README still described V2.1.11-era state: one board, three
    upload targets, BME280 as the only environmental sensor, no MQTT, no
    syslog, no coredump. The firmware has grown well past that.
    Updated to cover:
    - 4 board targets (heltec_v2, heltec_v2_4mb, feathers3_d, qtpy_esp32_pico)
    - Full environmental sensor matrix (SHT45, BMP581, BMP390, BME688, BME280)
2026-05-23 release.yml: fix hardcoded "20 artefacts" check after XIAO 5th board
    CI release job failed for V2.4.25 with:
    Error: expected 20 .bin artefacts, found 25
    I added the seeed_xiao_esp32s3 board to the build matrix earlier today
    but missed this downstream sanity check (4 boards x 5 artefacts = 20,
    now 5 boards x 5 = 25). All 5 board builds + cppcheck succeeded; only
    the artefact-count assertion fell over.
2026-05-29 V2.4.30: prompt MQTT reconnect on WiFi recovery; slow blind retry
    Router-reboot trace (2026-05-29, esp32-5965048) showed ~10s lag between
    GOT_IP and MQTT reconnect, plus 8 blind TLS connect attempts during the
    outage. Add mqtt_kick_reconnect() called from main.c's EV_GOT_IP handler
    to force an immediate reconnect on (re)association, and raise
    reconnect_timeout_ms 10s->30s to cut esp-tls context churn during outages
    (the kick owns recovery latency, the slow timer only the broker-down case).
2026-05-30 V2.5.3: republish HA discovery on /config Save (no reboot)
    A TX target toggled via plain "Save" starts uploading immediately (the TX
    path reads g_cfg fresh each cycle), but MQTT's rich-state JSON gating and the
    HA-discovery entity-presence predicates read CACHED enable flags that were
    only refreshed inside mqtt_init() (boot/reconnect). So a newly-enabled
    target's *_ok/*_att entities + JSON fields didn't appear in HA until a reboot.
    - New mqtt_apply_config(cfg): re-syncs the cached enable gates (HA-discovery,
2026-06-01 V2.5.8: GNSS receiver — GPS-primary time source + /status position
    New gnss.c/h driver (opt-in, all boards) auto-detects u-blox MAX-M10S
    (0x42, DDC) or CDTop PA1010D (0x10, NMEA stream) and binds the matching
    I2C transport. Shared checksum-validated NMEA parser (RMC + GGA),
    talker-ID-agnostic (GP*/GN*); drained ~1 Hz on the service tick.
    GPS-primary clock: settimeofday() from GNSS UTC on each valid fix,
    rate-limited to drift >= 2 s. SNTP keeps running as fallback, so NTP
2026-06-02 V2.5.12 (WIP): per-cycle raw-edge count profiler on the Geiger tube path
    Adds a permanent DIAG log line (emitted only on tube-enabled nodes): raw_edges
    (every count-ISR edge, before the 190us GMC_DEAD_TIME_US gate), rejected
    (= raw_edges - counts; ringing/double-counts), and an 8-bin edge-to-edge
    spacing histogram, via new tube_get_diag() snapshot/reset under mux_gmc.
    ISR cost is one volatile increment + a few comparisons per edge (negligible
    at ~1.2 cps, IRAM-safe); zeros on tube-disabled nodes.
2026-06-05 chore(gitignore): ignore loose root *.bin (OTA images, merge-bin output)
    Root-anchored /*.bin so local OTA images and _merge.cmd output
    (geiger_v2_merged_<board>.bin) can't be accidentally staged. All real release
    artefacts are built in CI and attached to the GitHub Release; none belong in the
    tree. build_*/ outputs were already ignored separately.
2026-06-09 V2.5.18: relocate heap-guard auto-reboot to the per-cycle resting snapshot
    The V2.5.14 heap guard sampled INTERNAL largest-free at ~1 Hz on the main
    task, so it caught the transient largest-free dip that any inbound HTTP
    connection causes -- the lwIP/TCP receive buffers are DMA-capable INTERNAL
    RAM, and a held-open GET /log (chunked stream) drops largest for its
    duration. Root-caused 2026-06-09 from the .150 syslog: each HEAP GUARD line
    landed 2-3 s after a GET /log from the monitor host, so the monitoring's own
2026-06-10 V2.5.20: full-codebase review batch - 5 bug fixes + hygiene
    Review IDs R1-R11 (see CHANGELOG.md for full WHAT/WHY):
    - R1: enable CONFIG_ESP_TLS_INSECURE + _SKIP_SERVER_CERT_VERIFY so MQTT
    TLS Mode D (skip verification) can actually connect; verified modes
    still verify fully
    - R2: percent-encode Radmon credentials (new util.h url_encode_query_value)
    - R3: FTPS TLS handshake gets socket timeouts + 30s wall-clock deadline
2026-06-13 status page: move "AP SSID" from System block to top of Network section
    The device's own fallback/AP-mode SSID (config ap_name) was rendering in
    the System block, where it read as out of place next to heap/NTP/reset
    info. Move it to the top of the Network block (above the joined-network
    "SSID:" line), and also surface it in the AP-mode Network branch where it
    is most relevant. Pure presentational move; no behaviour change.
2026-06-13 syslog + OTA: flash-time logging, local timestamps, boot-slot visibility (V2.5.28)
    - OTA: keep syslog up through the whole flash (drop syslog_stop from the
    teardown; mqtt_stop + log_ftp_pause remain the real heap win). Add a
    128 KB progress trace, a receive-complete summary (elapsed + KB/s),
    greppable "OTA FAILED: <stage>" headlines, and an "OTA SUCCESS" line —
    failed OTAs are now visible server-side, where they used to vanish.
    - syslog timestamp: when the clock is synced, emit local RFC 3339 with the
2026-06-14 V2.5.30: dead-time guard review hardening, PCNT mutual-exclusion, /config tidy
    Follow-up to the V2.5.30 dead-time-guard commit, addressing a local MAX code
    review plus user-requested UX fixes (all still V2.5.30, pre-tag):
    Review hardening (review #1-#5):
    - guard_removed now tallies only MARGINAL edges (those past the 190us gate), so
    it no longer double-credits the 50-190us afterpulses the gate already owned;
    it's a clean subset of `rejected` (counts_without_guard = counts + guard_removed).
2026-06-20 Bump to V2.5.34: FTP interval max 10090 + /config reports out-of-range fields
    - ftp_interval_min ceiling 1440 -> 10090 minutes (config_fields.def)
    - /config form label: "Upload interval (minutes) (Max 10090)"
    - config_post_apply_field() gains bool *out_rejected; X_U32/X_F32/X_U8 set it
    when a key matches but the value is out of range. config_post() accumulates
    those keys (+ the OLED-brightness step case) and shows a red "out of range,
    NOT saved (previous value kept)" banner via append_safe(), plus ESP_LOGW.
